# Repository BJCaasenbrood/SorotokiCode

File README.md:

<div align="center">  </div> <br/>

[**Sorotoki**](https://bjcaasenbrood.github.io/SorotokiPage/) is an open-source MATLAB toolkit for soft robotics that includes an array of tools for design, modeling, and control. Due to its scientific diversity, it can be challenging for new researchers to quickly familiarize themselves with multiple scientific areas. With the aim to lower this threshold, Sorotoki aims to incorporate multiple layers of soft robotics research into one compact toolkit. Examples include: continuum mechanics, dynamic systems and control theory, topology optimization, computer graphics, and much more to come! The combination provides a highly flexible programming environment and will hopefully aid the development of novel soft robotic research.

#### Installation via Matlab Package Installer (MPI)
The toolkit is easy to install using the Matlab Package Installer ([mpi](https://github.com/mobeets/mpm)). Please follow the [**Installation Guide**](https://bjcaasenbrood.github.io/SorotokiCode/install/).

## Applications highlights

- [x] [Sdf](https://github.com/BJCaasenbrood/SorotokiSdf) - Implicit modeling with Signed Distance Functions (SDFs),
- [x] [Fem](https://github.com/BJCaasenbrood/SorotokiFem) - Finite element method (FEM) using hyper-elastic materials,
- [x] [Topo](https://github.com/BJCaasenbrood/SorotokiFem) - Topology optimization of (pressure-driven) soft robots,
- [x] [Model](https://github.com/BJCaasenbrood/SorotokiModel) - Dynamical modeling through geometric theory,
- [x] [Control](https://github.com/BJCaasenbrood/SorotokiCode) - Real-time control of soft robots via Raspi-interface,
- [x] [GModel](https://github.com/BJCaasenbrood/MatlabGraphicalModel) - Fast graphics rendering with responsive textures.

## What can it do?

## Citation

If you are planning on using Sorotoki in your (academic) work, please consider citing the toolkit  

```bibtex
@article{Caasenbrood2024,
	author = {Caasenbrood, Brandon J. and Pogromsky, Alexander Y. and Nijmeijer, Henk},
	title = {{Sorotoki: A Matlab Toolkit for Design, Modeling, and Control of Soft Robots}},
	journal = {IEEE Access},
	volume = {12},
	pages = {17604--17638},
	year = {2024},
	publisher = {IEEE},
	doi = {10.1109/ACCESS.2024.3357351}
}
```

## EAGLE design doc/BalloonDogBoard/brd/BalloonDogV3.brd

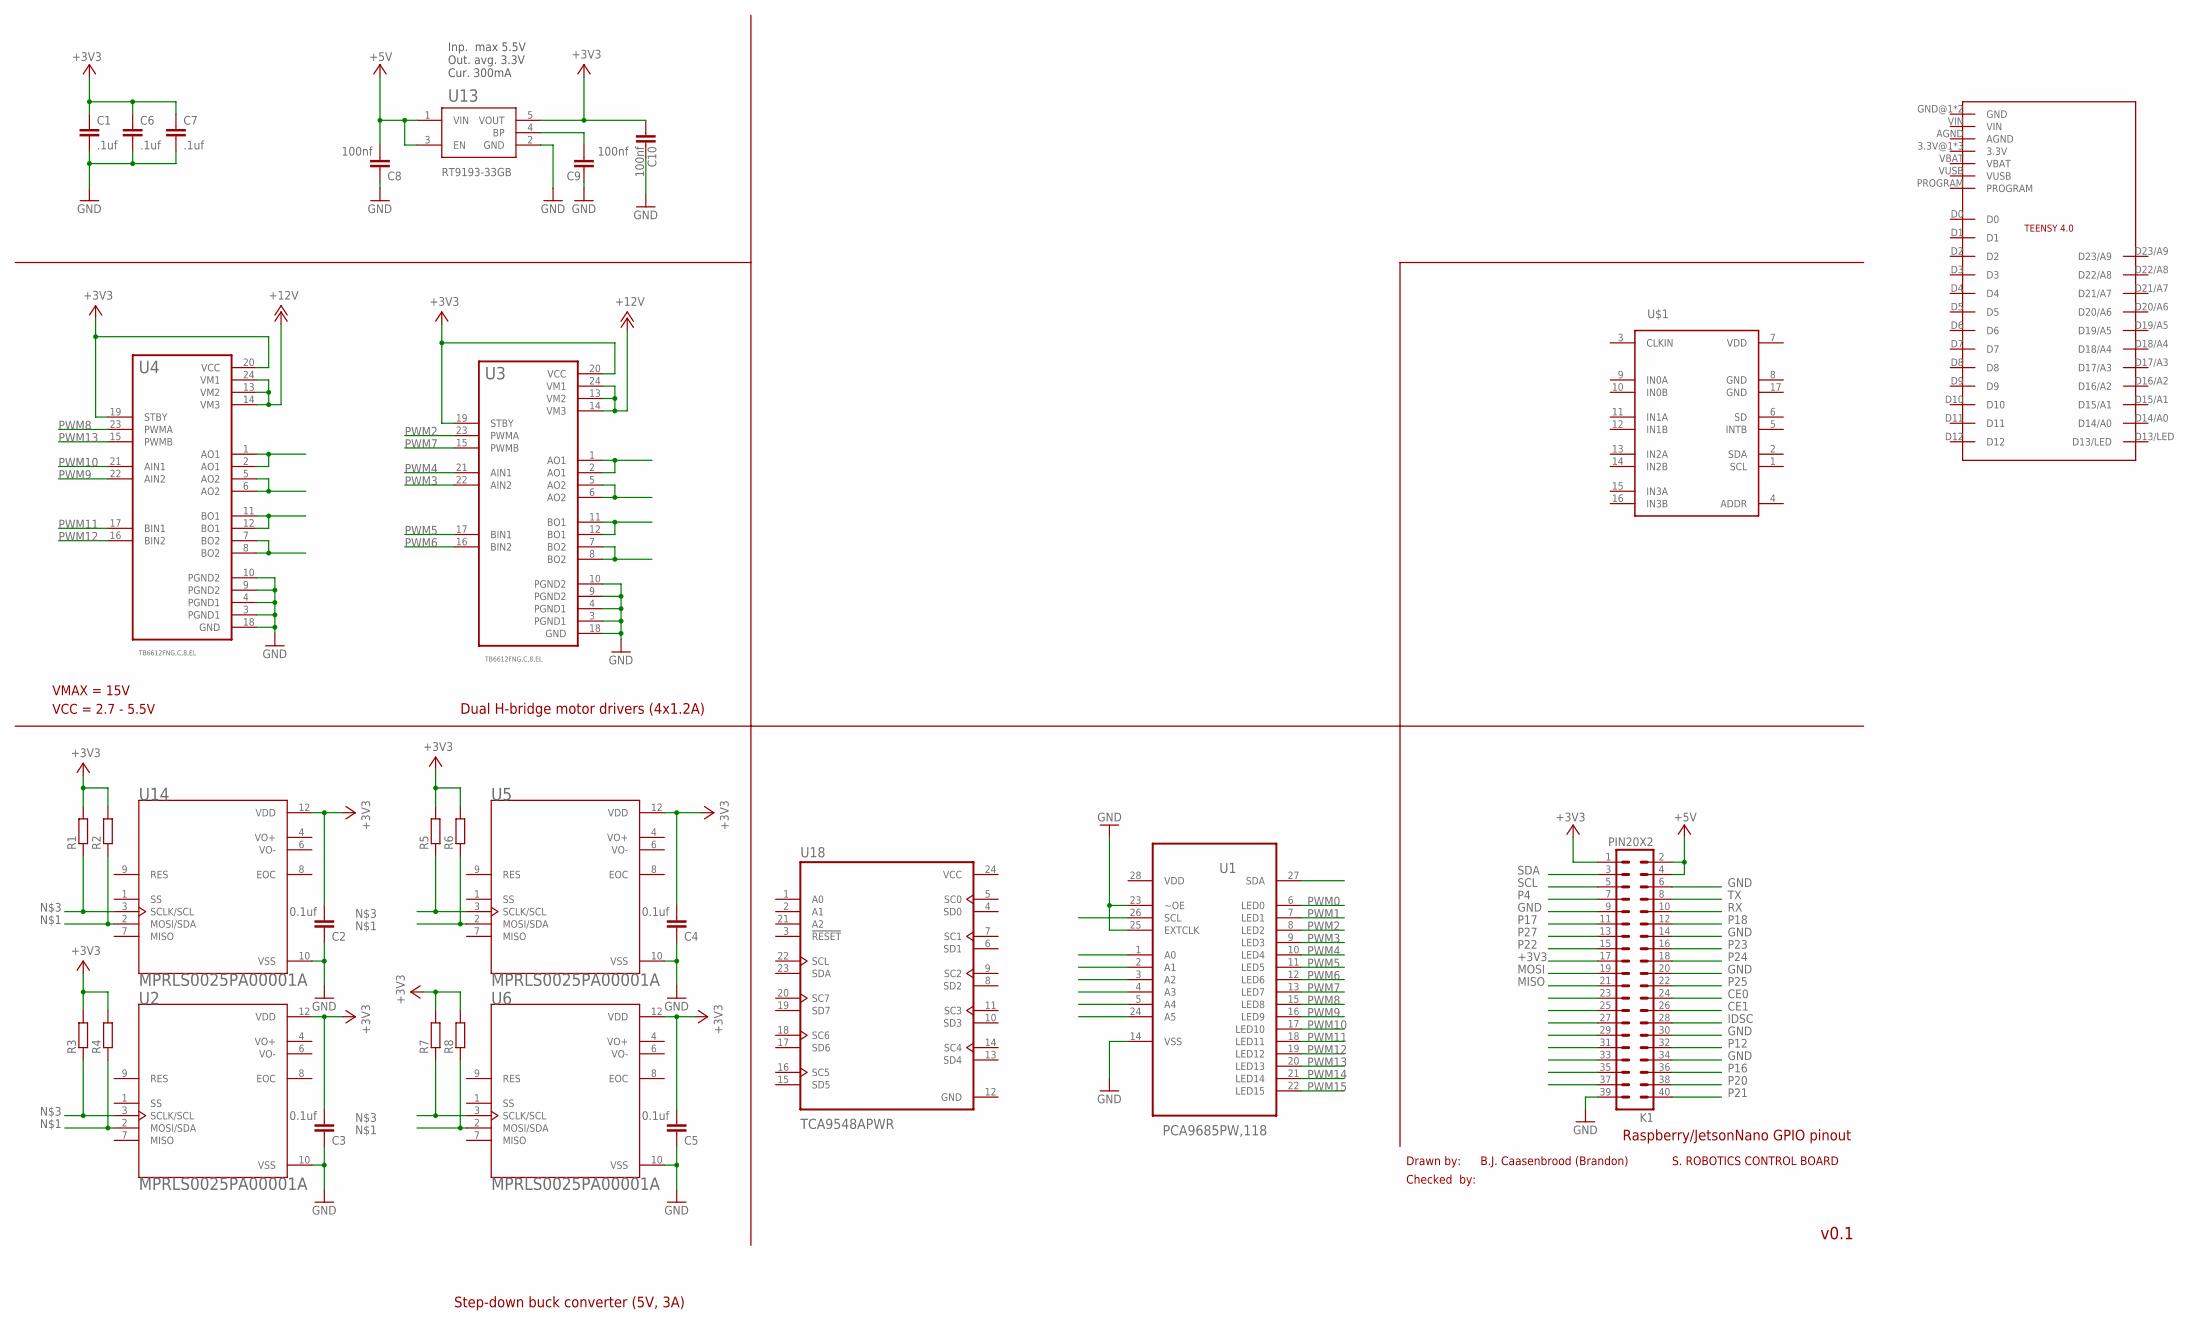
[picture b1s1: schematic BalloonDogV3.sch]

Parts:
C1, C6, C7: .1uf; C0805K
C2, C3, C4, C5: 0.1uf; C0603
C8, C9, C10: 100nf; C0603
K1: PIN20X2; PIN_20X2
R1, R2, R3, R4, R5, R6, R7, R8: R-EU_R0603; R0603
U1: PCA9685PW,118; SOP65P640X110-28N
U2, U5, U6, U14: MPRLS0025PA00001A; XDCR_MPRLS0025PA00001A
U3, U4: TB6612FNG,C,8,EL; SOP65P760X160-24N
U13: RT9193-33GB; SOT94P279X129-5N
U18: TCA9548APWR; SOP65P640X120-24N
U$1: LDC1614
U$2: TEENSY4.0

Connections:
+3V3: C1.1, C2.2, C3.2, C4.2, C5.2, C6.1, C7.1, C10.2, K1.1, K1.17, R1.2, R2.2, R3.2, R4.2, R5.2, R6.2, R7.2, R8.2, U2.12 (VDD), U3.19 (STBY), U3.20 (VCC), U4.19 (STBY), U4.20 (VCC), U5.12 (VDD), U6.12 (VDD), U13.5 (VOUT), U14.12 (VDD)
+5V: C8.2, K1.2, K1.4, U13.1 (VIN), U13.3 (EN)
+12V: U3.13 (VM2), U3.14 (VM3), U3.24 (VM1), U4.13 (VM2), U4.14 (VM3), U4.24 (VM1)
CE0: K1.24
CE1: K1.26
GND: C1.2, C2.1, C3.1, C4.1, C5.1, C6.2, C7.2, C8.1, C9.1, C10.1, K1.6, K1.9, K1.14, K1.20, K1.30, K1.34, K1.39, U1.14 (VSS), U1.23 (~OE), U1.25 (EXTCLK), U2.10 (VSS), U3.3 (PGND1), U3.4 (PGND1), U3.9 (PGND2), U3.10 (PGND2), U3.18 (GND), U4.3 (PGND1), U4.4 (PGND1), U4.9 (PGND2), U4.10 (PGND2), U4.18 (GND), U5.10 (VSS), U6.10 (VSS), U13.2 (GND), U14.10 (VSS), U18.12 (GND)
IDSC: K1.28
MISO: K1.21
MOSI: K1.19
unnamed: R2.1, R4.1, R6.1, R8.1, U2.2 (MOSI/SDA), U5.2 (MOSI/SDA), U6.2 (MOSI/SDA), U14.2 (MOSI/SDA)
unnamed: R1.1, R3.1, R5.1, R7.1, U2.3 (SCLK/SCL), U5.3 (SCLK/SCL), U6.3 (SCLK/SCL), U14.3 (SCLK/SCL)
unnamed: U3.1 (AO1), U3.2 (AO1)
unnamed: U3.5 (AO2), U3.6 (AO2)
unnamed: U3.11 (BO1), U3.12 (BO1)
unnamed: U3.7 (BO2), U3.8 (BO2)
unnamed: U4.1 (AO1), U4.2 (AO1)
unnamed: U4.5 (AO2), U4.6 (AO2)
unnamed: U4.11 (BO1), U4.12 (BO1)
unnamed: U4.7 (BO2), U4.8 (BO2)
unnamed: C9.2, U13.4 (BP)
P4: K1.7
P12: K1.32
P16: K1.36
P17: K1.11
P18: K1.12
P20: K1.38
P21: K1.40
P22: K1.15
P23: K1.16
P24: K1.18
P25: K1.22
P27: K1.13
PWM0: U1.6 (LED0)
PWM1: U1.7 (LED1)
PWM2: U1.8 (LED2), U3.23 (PWMA)
PWM3: U1.9 (LED3), U3.22 (AIN2)
PWM4: U1.10 (LED4), U3.21 (AIN1)
PWM5: U1.11 (LED5), U3.17 (BIN1)
PWM6: U1.12 (LED6), U3.16 (BIN2)
PWM7: U1.13 (LED7), U3.15 (PWMB)
PWM8: U1.15 (LED8), U4.23 (PWMA)
PWM9: U1.16 (LED9), U4.22 (AIN2)
PWM10: U1.17 (LED10), U4.21 (AIN1)
PWM11: U1.18 (LED11), U4.17 (BIN1)
PWM12: U1.19 (LED12), U4.16 (BIN2)
PWM13: U1.20 (LED13), U4.15 (PWMB)
PWM14: U1.21 (LED14)
PWM15: U1.22 (LED15)
RX: K1.10
SCL: K1.5
SDA: K1.3
TX: K1.8
VCC: U18.24 (VCC)
VDD: U1.28 (VDD)

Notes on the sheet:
Drawn by:
Checked by:
S. ROBOTICS CONTROL BOARD
B.J. Caasenbrood (Brandon)
v0.1
Step-down buck converter (5V, 3A)
Dual H-bridge motor drivers (4x1.2A)
Raspberry/JetsonNano GPIO pinout
VMAX = 15V
VCC = 2.7 - 5.5V
Inp. max 5.5V Out. avg. 3.3V Cur. 300mA

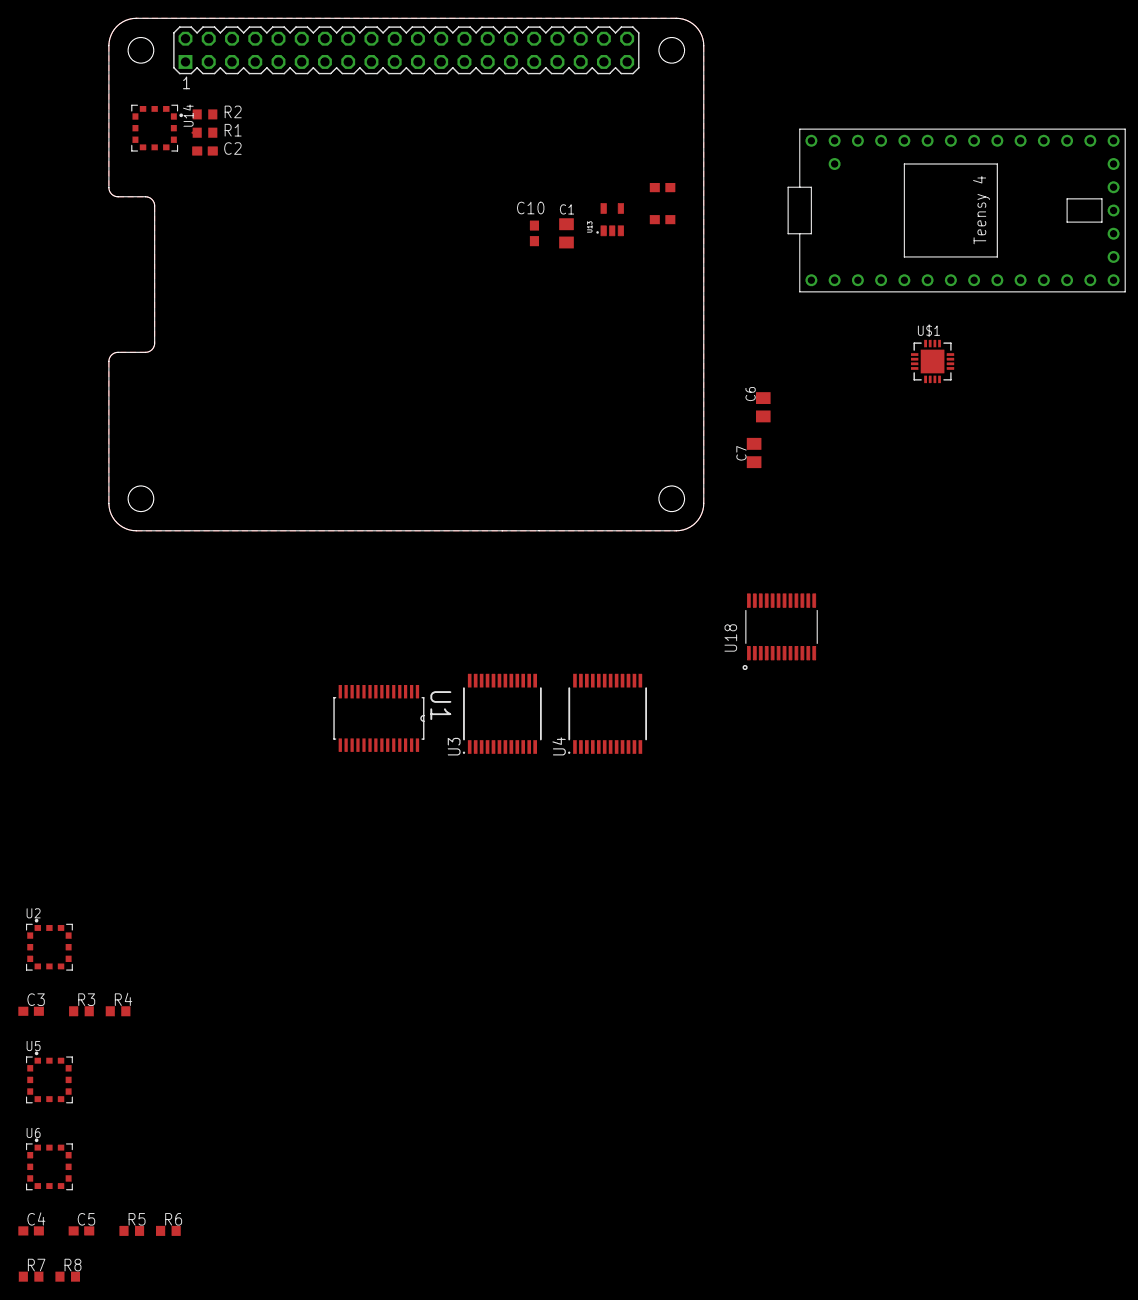
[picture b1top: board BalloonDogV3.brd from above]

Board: 4 copper layers, 65.0 x 56.0 mm, 30 parts (0 on the bottom side), 27 nets.

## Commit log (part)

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2020-05-27 push
2020-07-29 added balloondog class
2020-08-31 removed matlab.mat
2020-09-03 updated sorotoki.m
2020-09-08 updated mdl_demo and Model.m
2020-09-15 null file removal
2020-09-21 added beta
2020-10-26 Added Inverse-Kinematic rigging for Cosserat models
2020-11-05 Change to 'Just-The-Docs' gitpage
2020-11-05 push just-the-docs page
2020-11-07 Added documentation
2020-11-10 updated gitpage
2020-11-18 config.yml change
2020-12-15 updated gitpages
2021-01-05 backup push for Model.lib change
2021-01-14 applied major updates to c++ model of Model.lib - requires cmake to compile - major functions are distributed into seperate classes - improved compile speed
2021-02-08 1) Changed sorotoki.m to report on missing toolboxes 2) Added AddConstraint('Pressure')! Finally! 3) updated vappend to input desired appending order
2021-02-09 added writeMatrixFile.m
2021-02-16 Updated installer to check installed toolboxes for older Matlab versions
2021-03-19 Added paper files for JOSS
2021-03-25 transfer
2021-04-22 Refiled the gitpage documention folder
2021-05-11 1_ Updated documentation 2_ Modified 2D-FEM scripts 3_ Added a new 3D FEM-element: C3T4
2021-05-27 1) Updated demo scripts 2) Added new verification functionalities for Mesh and Fem
2021-07-29 removed redundant files
2021-07-30 added SDF option to the FEM.m for initial topologies
2021-08-09 Updated documentation of the Gitpage
2021-09-03 small updated to example section
2021-09-10 updated small typo
2021-09-28 Bump nokogiri from 1.12.2 to 1.12.5
    Bumps [nokogiri](https://github.com/sparklemotion/nokogiri) from 1.12.2 to 1.12.5.
    - [Release notes](https://github.com/sparklemotion/nokogiri/releases)
    - [Changelog](https://github.com/sparklemotion/nokogiri/blob/main/CHANGELOG.md)
    - [Commits](https://github.com/sparklemotion/nokogiri/compare/v1.12.2...v1.12.5)
    ---
    updated-dependencies:
2021-11-11 - Added 'Displace' to FEM.AddConstraint to replace DescribedDisplacement boolean. Now you can use fem.AddConstraint('Diplace',...) - updated documentation
2021-11-29 updated FEM.m; attempt to add Newmark solver
2021-12-08 updated Shaped.m
2022-01-24 pushing update 2.24.01
2022-02-08 pushing small update
2022-02-26 Bump nokogiri from 1.12.5 to 1.13.3
    Bumps [nokogiri](https://github.com/sparklemotion/nokogiri) from 1.12.5 to 1.13.3.
    - [Release notes](https://github.com/sparklemotion/nokogiri/releases)
    - [Changelog](https://github.com/sparklemotion/nokogiri/blob/main/CHANGELOG.md)
    - [Commits](https://github.com/sparklemotion/nokogiri/compare/v1.12.5...v1.13.3)
    ---
    updated-dependencies:
2022-03-31 removed some large gifs
2022-04-04 Documentation update
2022-04-04 fixed logo
2022-04-04 logo
2022-04-05 removed .m
2022-04-07 fixed one file in sorotoki.m :)
2022-04-17 updated PneuNet and updated modal extraction
2022-05-06 updated Model scripts added paper.md
2022-05-17 pushing update 2.05.17
2022-05-19 added new
2022-05-20 small update to verifySorotoki.m and sorotoki.m
2022-05-26 Added dual pneunet optimization script
2022-07-22 preparing for 2.07.22 release
2022-08-10 prepping 2.08.10 update
2022-09-15 Fix mex compiler issue for LocalsNHFast.m
    Solved issue when compiling mex: ??? Dimension 1 is fixed on the left-hand side but varies on the right ([1 x 1] ~= [:? x 1]).
    Problem is issued here: https://imathworks.com/matlab/matlab-matlab-r2015a-coder-errordimension-1-is-fixed-on-the-left-hand-side-but-varies-on-the-right-1024-x-1-x-1/
2022-09-24 Update to Fem.addTendon
    update is compatible for 3D fem simulations
2022-12-08 preparing for (major) V3 release :0
2022-12-09 Drop files from .gitignore
2022-12-20 Fixed readme.md
2023-01-20 rename the colormap to cmap_...
2023-09-11 Update the installer function to accept optional arguments for different actions such as install/remove/disable/update/build. Implement functions to handle installation/removal of packages using MPM.
2023-09-11 Deployed 2c04ab2 with MkDocs version: 1.4.2
2023-09-12 Refactor navigation structure in mkdocs.yml
    - Updated the navigation structure in mkdocs.yml
    - Renamed "Signed Distance Function" to "Sdf.m"
    - Reorganized the subpages under "Sdf.m"
    - Added new section "Mesh.m" with its respective subpages
    - Added new section "Fem.m" with its respective subpages
    - No changes made to other sections or pages
2023-09-12 feat: Add src to .gitignore and include sorotokifem in requirements.txt
    - Added "src" to the .gitignore file to exclude it from version control.
    - Included "sorotokifem" in the requirements.txt file for dependency management.
2023-09-19 Update requirements.txt and mkdocs.yml
    - Added "sorotokimodel" to requirements.txt
    - Updated navigation structure in mkdocs.yml
    - Added new pages for fem/solid.md, fem/hyperelast.md, fem/solvers.md, fem/inverse.md, shapes/shapes.md, and model/model.md
    - Enabled video mute and controls in mkdocs-video plugin configuration
2023-09-19 Deployed 50db06b with MkDocs version: 1.4.2
2023-09-27 Update sorotoki.m installer function
    - Fix a typo in the comment
    - Update the description of how to start the installation
    - Add a new command for disabling the toolkit while keeping source files
    - Update the list of required additional toolboxes
2023-10-03 Cleaned @sorotoki main script by introducing a private folder
2023-10-04 feat: Add CircleCI configuration file and update VSCode settings
    - Added `.circleui/config.yml` file to configure CircleCI version 2.1
    - Updated `.vscode/settings.json` file to exclude certain directories from file watching
2023-10-04 Refactor code for checking and installing missing MPM packages
    - Updated the `checkPackagesMPM` function to include a conditional check for `auto_approve`
    - Added an input prompt to confirm installation of missing MPM packages if `auto_approve` is false
    - Renamed the function `installMissingPackgeMPM` to `installMissingPackageMPM`
    Refactor code for checking and installing missing Sorotoki packages
    - Updated the `checkSoroPackages` function to include a conditional check for `auto_approve`
    - Added an input prompt to confirm installation of missing MPM packages if `auto_approve` is false
2023-10-04 Error handling when mpm.mat does not exist
    - Refactored the code to handle errors when loading package information from `mpm.mat`
    - Added a try-catch block to handle exceptions and return empty arrays if an error occurs
    - Updated the function `installSorotoki` to only retrieve package names from `getPackagesInformationMPM()`
2023-10-04 Refactor buildSorotokiMex and runSorotokiTest functions
    - Updated the buildSorotokiMex function to include a global variable "auto_approve" and added conditional logic based on its value.
    - Refactored the paths in the buildSorotokiMex function to use lowercase directory names.
    - Updated the runSorotokiTest function to use lowercase suite names.
    This commit refactors the buildSorotokiMex and runSorotokiTest functions, adding a global variable and updating paths and suite names.
2023-10-04 Delete draft-pdf.yml workflow
    This commit removes the draft-pdf.yml workflow file, which was responsible for building a draft PDF of a paper. The workflow included steps for checking out the repository, building the PDF using ope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
2023-10-04 Refactor code to use `which` instead of `whereis`
    - Replaced `whereis` with `which` in line 6
    - Updated variable name from `installFile` to `installPath`
    - Removed unnecessary substring operation on `installPath`
    This commit refactors the code in the sorotoki.m file by replacing the deprecated function whereis with which. It also updates a variable name and removes an unnecessary substring operation.
    Refactor code to use `which` instead of `whereis`
    - Replaced `whereis` with `which` in line 6
2023-10-04 Refactor buildSorotokiMex.m for improved readability and maintainability.
    The commit message is too long. Please limit it to 50 characters or less.
2023-10-04 Refactor buildSorotokiMex and runSorotokiTest functions
    - Refactored buildSorotokiMex function to use the installPath variable instead of the path variable
    - Refactored runSorotokiTest function to accept the installPath variable as an argument
2023-10-04 Increase size of softrobot.svg image and add badges to README.md
    The commit increases the width of the softrobot.svg image in the README.md file from 700 to 850 pixels. It also adds badges for Sorotoki documentation, MATLAB workflow, CircleCI, and GitHub license.
2023-10-05 changed ci.yml to CI_Linux.yml
2023-10-05 added assets to sorotoki
2023-10-05 minor updates to readme.md
2023-10-06 moved shapes preset to sorotoki main folder
2023-10-12 feat: Add matrix tests to CircleCI config
    This commit adds a new workflow called "matrix-tests" to the CircleCI configuration file. The workflow includes a job named "test" that runs tests for different versions of a software, specifically R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
2023-10-12 Update requirements.txt: Add sorotokicontrol and sorotokibots
    This commit adds two new dependencies, sorotokicontrol and sorotokibots, to the requirements.txt file.
2024-01-09 Deployed 8f6f6a2 with MkDocs version: 1.4.2
2024-01-23 Add paper.pdf
    This commit adds a new file, paper.pdf.
2024-01-23 Refactor suzumori_walker.m to generate Mesh without try-catch block
    The code changes remove the unnecessary try-catch block and generate a Mesh object directly. This simplifies the code and improves readability.
2024-02-02 Refactor test runner to suppress warnings
    The code changes in `runSorotokiTest.m` refactor the test runner to suppress warnings. This is achieved by turning off warnings before running the tests and then turning them back on afterwards. The 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
2024-02-02 Refactor package installation and test result display
    - Refactored the `installMissingPackageMPM` function to include the 'sorotokicontrol' case for installing a specific package from a GitHub repository.
    - Removed unnecessary log.info() calls in the `runSorotokiTest` function.
    - Updated the `testsuite` variable in the `sorotoki` function to exclude 'control' and 'bots' tests.
2024-02-02 Deployed 38ea3cf with MkDocs version: 1.4.2
2024-02-26 Update folder names and references from "mpm" to "mpi" for consistency. Fix conditional check in sorotoki.m to correctly detect the presence of "mpm".
2024-02-26 Update installation instructions to use Matlab Package Installer (MPI).
    The commit changes the installation method from Matlab Package Manager (MPM) to Matlab Package Installer (MPI) for easier toolkit installation.
2024-03-07 Update prompt handling to check the first element. Refactor testsuite array in sorotoki function.
2024-04-08 Add function to retrieve commit information from GitHub
    A new function was added to fetch commit details including SHA and date from a specified repository on GitHub using the API.
2024-04-08 Update package checking and installation logic in Sorotoki library. Improve handling of outdated packages, prompting for updates if needed.
2024-04-08 Update CITATION.cff with Sorotoki software details and metadata for citation. Include authors, identifiers, repository link, abstract, keywords, and license information.
2024-04-08 Update CITATION.cff with preferred article citation details and metadata for Sorotoki Matlab Toolkit.
2024-04-09 Deployed 3525150 with MkDocs version: 1.4.2
2024-04-19 Add new MATLAB versions to workflow matrix
    - Include new MATLAB versions R2021a, R2022a, and R2023b in the workflow matrix parameters for version selection.
2024-04-23 Add realtime control loop example with setpoint and data reading. Set frequency to 60Hz, execute control loop with PIDs for 3 axes.
2024-04-23 Update MATLAB orb version in CircleCI config
    Changed MATLAB orb version from dev:v1-beta to 1.1.1 in the CircleCI configuration file.
2024-04-24 Fixed fem_eigen_comp.m, compute internal stresses, and show Von Mises results.
2024-04-24 Deployed f39f0c1 with MkDocs version: 1.4.2
2024-04-24 Deployed 0e15ecd with MkDocs version: 1.4.2
2024-04-25 Refactor mex build functions for improved clarity and naming.
    - Renamed functions for building CurveSweep, ForwardKin, and Lagrangian mex files to enhance readability and maintainability.
2024-04-25 Update mesh generation simplification tolerance to 0.0125.
    The commit modifies the mesh generation function by adjusting the simplification tolerance parameter from 0.0085 to 0.0125 for improved mesh quality and accuracy.
